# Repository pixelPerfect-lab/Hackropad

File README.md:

# Hackropad
The hackropad is a 3 key macropad with a rotary encoder. It connects to your PC with a USB type B cable, and is very compact. I designed this over 11 and a half hours, and in my opinion looks acceptable.
Part	| What it's for	| Qty	| Unit	| Total |	Vendor
--------|---|---|---|---|---
RP2040 | MCU | 1 | $0.76 | $0.76 | DigiKey
4Mb flash memory | Flash memory for raspberry pi | 1	| $1.34	| $1.34 |	DigiKey
3.3V voltage regulator | Micro USB type b power |	1	| $0.62	| $0.62 |	DigiKey
Micro-USB connector	| Connection to PC and power |	1	| $0.81 |	$0.81 |	DigiKey
Rotary encoder with push button |	Rotary Encoder input | 1 |	$2.69 |	$2.69 |	DigiKey
Cherry MX2A Brown keyboard switch |	Button inputs |	3 |	$1.75 |	$5.25 |	DigiKey
Momentary reset switch |	Resetting the Raspberry Pi |	1 |	$0.35 |	$0.35 |	DigiKey
2-pin header, 2.54 mm	| Short to boot	| 1	| $0.21 |	$0.21 |	DigiKey
12 MHz crystal |	Crystal for clocking the RP2040	| 1 | 	$0.69 |	$0.69 |	DigiKey
Passive Components |	Capacitors and resistors (80 total per set) |	1	| $4.55 |	$4.55 |	DigiKey
Parts subtotal |	—	| —	| — |	$17.27 |	—
Tax & shipping	| —	| — |	— |	$0.00 |	—
Total |	—	| —	| —	| $17.27 |	—

https://cad.onshape.com/documents/e98056e3a4491591a6f8bf1e/w/48743fa81ab57436ecb89123/e/8a25d650e3180fe18e477bea

Half-Life is a 10 week long hardware adventure, where teens aged 13-18 can learn about how to create and ship various projects, with rewards along side it, up to 100 dollars of project funding, and a 3D printer as a final reward.

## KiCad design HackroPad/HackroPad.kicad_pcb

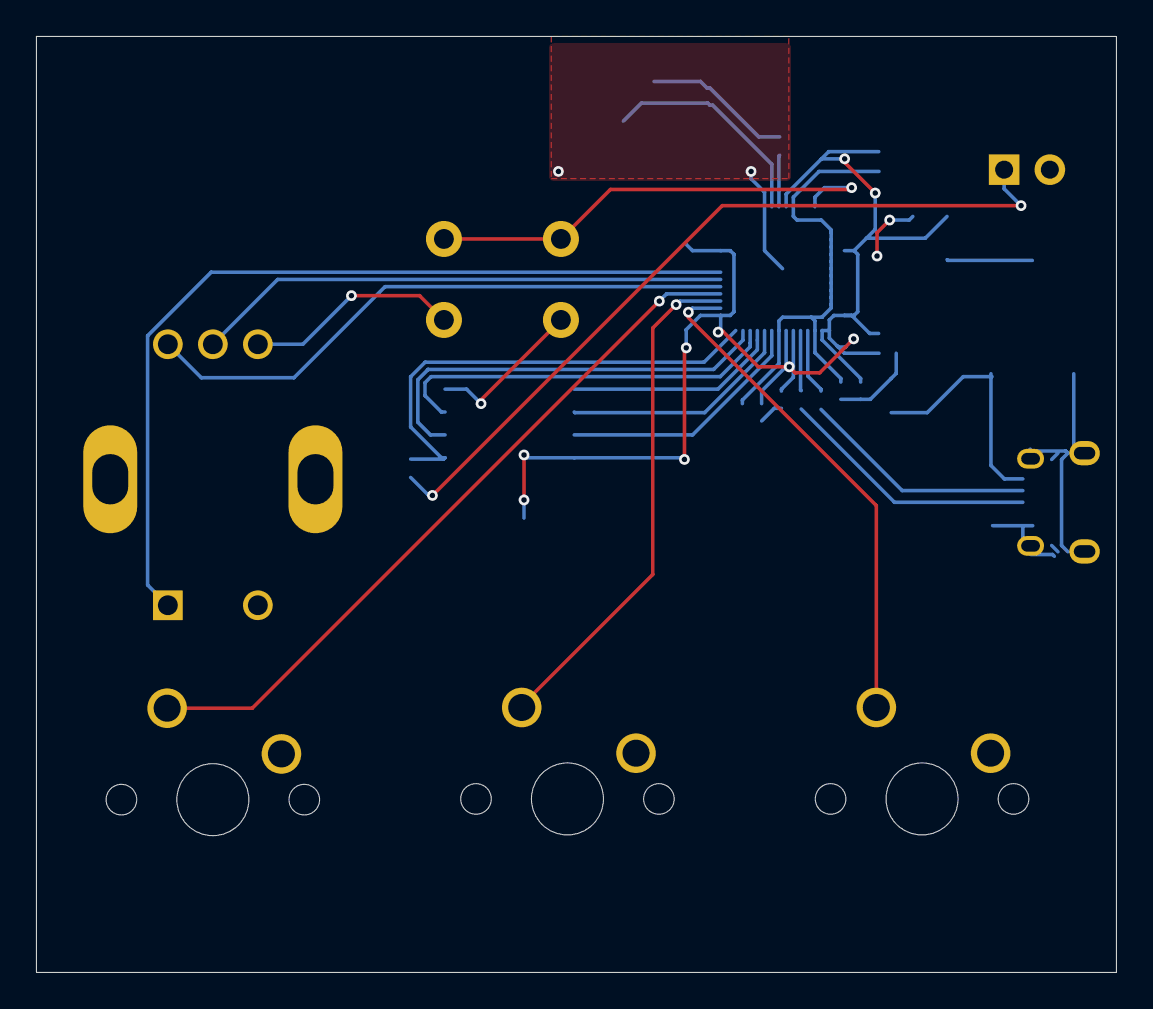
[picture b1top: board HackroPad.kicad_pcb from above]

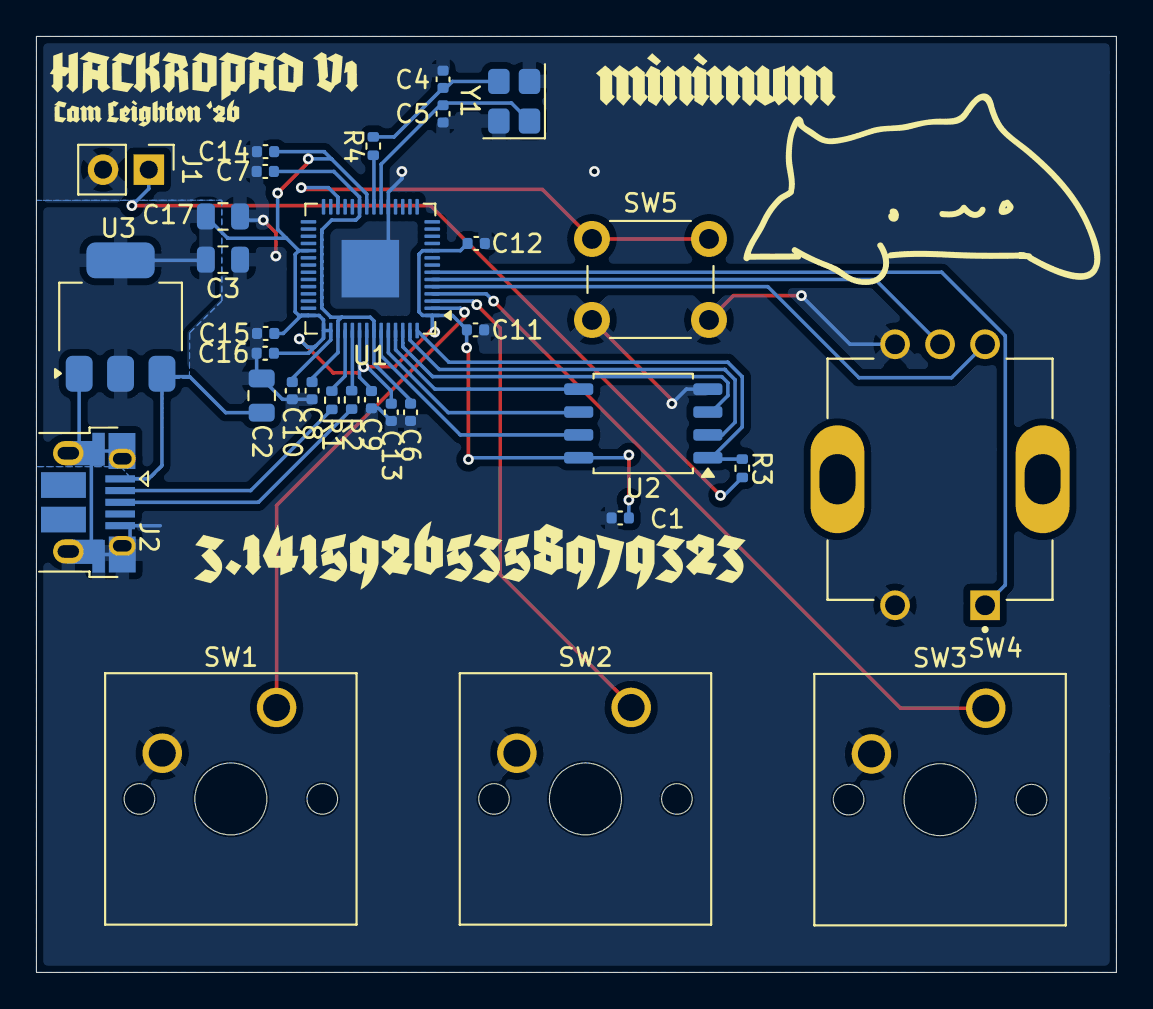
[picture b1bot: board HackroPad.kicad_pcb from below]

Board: 2 copper layers, 60.0 x 52.0 mm, 32 parts (32 on the bottom side), 25 nets.

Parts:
C1, C6, C7, C9, C11, C12, C13, C14, C15, C16: 100n; C_0402_1005Metric
C2, C3, C17: 10u; C_0805_2012Metric
C4, C5: 15p; C_0402_1005Metric
C8, C10: 1u; C_0402_1005Metric
J1: TSW-102-07-G-S; PinHeader_1x02_P2.54mm_Vertical
J2: 10103594-0001LF; USB_Micro-B_Amphenol_10103594-0001LF_Horizontal
R1, R2: 27; R_0402_1005Metric
R3, R4: 1k; R_0402_1005Metric
SW1, SW2, SW3: Cherry MX2A; SW_Cherry_MX_1.00u_PCB
SW4: PEC11R-4220F-S0024-ND; XDCR_PEC11R-4220F-S0024
SW5: Momentary; SW_PUSH_6mm
U1: RP2040; QFN-56-1EP_7x7mm_P0.4mm_EP3.2x3.2mm
U2: W25Q32JVSS; SOIC-8_5.3x5.3mm_P1.27mm
U3: NCP1117ST33T3G; SOT-223-3_TabPin2
Y1: 12MHz; Crystal_SMD_3225-4Pin_3.2x2.5mm

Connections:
+1V1: C6.1, C7.1, C8.1, U1.23 (DVDD), U1.45 (VREG_VOUT), U1.50 (DVDD)
+3V3: C1.1, C3.1, C9.1, C10.1, C11.1, C12.1, C13.1, C14.1, C15.1, C16.1, C17.1, U1.1 (IOVDD), U1.10 (IOVDD), U1.22 (IOVDD), U1.33 (IOVDD), U1.42 (IOVDD), U1.43 (ADC_AVDD), U1.44 (VREG_VIN), U1.48 (USB_VDD), U1.49 (IOVDD), U2.8 (VCC), U3.2 (VO)
/GPIO0: SW1.1, U1.2 (GPIO0)
/GPIO1: SW2.1, U1.3 (GPIO1)
/GPIO2: SW3.1, U1.4 (GPIO2)
/GPIO3: SW4.A, U1.5 (GPIO3)
/GPIO4: SW4.C, U1.6 (GPIO4)
/GPIO5: SW4.1, U1.7 (GPIO5)
/QSPI_SCLK: U1.52 (QSPI_SCLK), U2.6 (CLK)
/QSPI_SD0: U1.53 (QSPI_SD0), U2.5 (DI/IO_{0})
/QSPI_SD1: U1.55 (QSPI_SD1), U2.2 (DO/IO_{1})
/QSPI_SD2: U1.54 (QSPI_SD2), U2.3 (~WP/IO_{2})
/QSPI_SD3: U1.51 (QSPI_SD3), U2.7 (~HOLD/~RESET/IO_{3})
/QSPI_SS: R3.2, U1.56 (~QSPI_SS), U2.1 (~CS)
/RUN: SW5.1, U1.26 (RUN)
/USB_D+: J2.3 (D+), R2.1
/USB_D-: J2.2 (D-), R1.1
/XIN: C5.2, U1.20 (XIN), Y1.1
/XOUT: R4.2, U1.21 (XOUT)
GND: C1.2, C2.2, C3.2, C4.1, C5.1, C6.2, C7.2, C8.2, C9.2, C10.2, C11.2, C12.2, C13.2, C14.2, C15.2, C16.2, C17.2, J1.2, J2.5 (GND), J2.SH (Shield), SW1.2, SW2.2, SW3.2, SW4.2, SW4.B, SW5.2, U1.19 (TESTEN), U1.57 (GND), U2.4 (GND), U3.1 (GND), Y1.2 (G), Y1.4 (G)
unnamed: C4.2, R4.1, Y1.3
unnamed: J1.1, R3.1
unnamed: R1.2, U1.46 (USB_DM)
unnamed: R2.2, U1.47 (USB_DP)
VBUS: C2.1, J2.1 (VBUS), U3.3 (VI)
